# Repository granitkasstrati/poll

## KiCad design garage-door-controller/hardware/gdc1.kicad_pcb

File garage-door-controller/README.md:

# gdc1: open-source smart garage door controller (rev A)

A local-first retrofit controller that works with the opener you already have. A dry-contact relay presses the
wall button. Three opto-isolated reed inputs sense the door. An ESP32-S3 connects it to MQTT/Home Assistant,
with no cloud.

| Path | What |
|---|---|
| `docs/DESIGN.md` | requirements → hardware map, **calculations**, pin map, **what to verify**, bring-up, installation |
| `docs/PCB.md` | floor plan, layout rules, DRC status, how to regenerate |
| `hardware/gdc1.kicad_pro` | KiCad 7 project (schematic + PCB) |
| `hardware/fab/` | Gerbers + drill (zip), BOM CSV, pick-and-place, schematic/PCB PDFs, renders |
| `hardware/gen/` | Python generators. `design.py` is the single source of truth for parts and nets |
| `firmware/board_pins.h` | GPIO map for the ESP-IDF firmware (Phase 2/3 of the plan) |

**Board:** 105 × 85 mm, 2 layers, 1.6 mm FR4, 1 oz. 122 parts, mostly SMD 0603/0805/1206. The fine-pitch
parts are the ESP32-S3 module, the USB-C receptacle and the BME280 LGA (hot air recommended for that one).

**Highlights**
* Input: 9–36 VDC (either polarity) or 24 VAC → TPS54360 60 V buck. A USB-C alone also powers and flashes the board.
* Relay drive is AC-coupled in hardware, so a crashed MCU cannot hold the opener button "pressed" (SR4).
* Door inputs run from an isolated 1 W DC/DC, with a 2 mm isolation fence on the PCB. Each input has an LED
  that lights when its reed is closed, with or without firmware.
* Pre-close warning: on-board buzzer + red LED, plus a switched 12/24 V output for a strobe at the door (UL 325).
* BME280 sits in a thermally slotted corner. A Qwiic port takes a ToF sensor, and an expansion header
  takes a CT clamp or UART.

Licences: hardware CERN-OHL-S-2.0, firmware/scripts MIT.

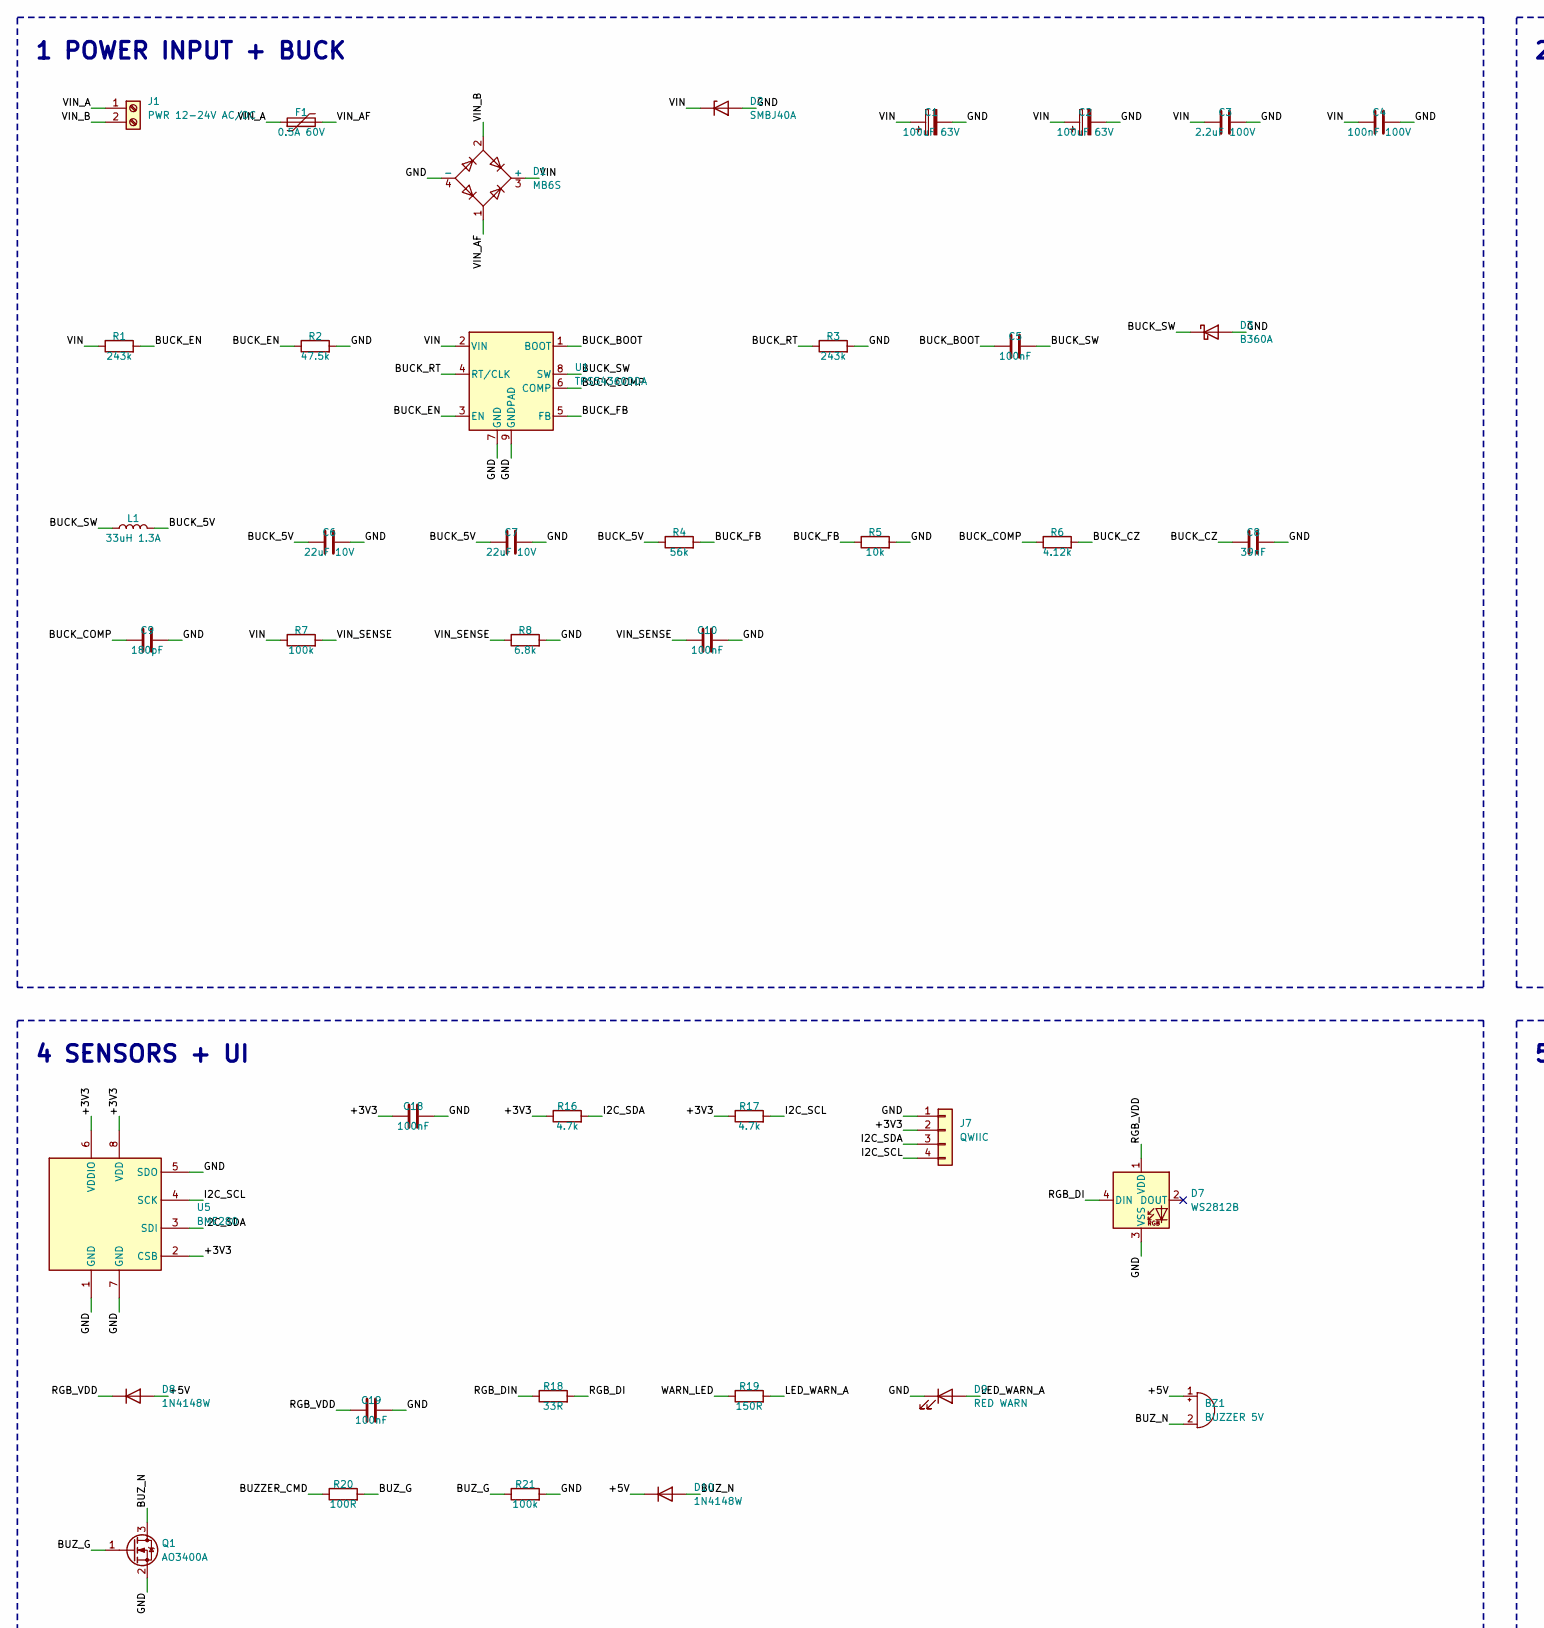
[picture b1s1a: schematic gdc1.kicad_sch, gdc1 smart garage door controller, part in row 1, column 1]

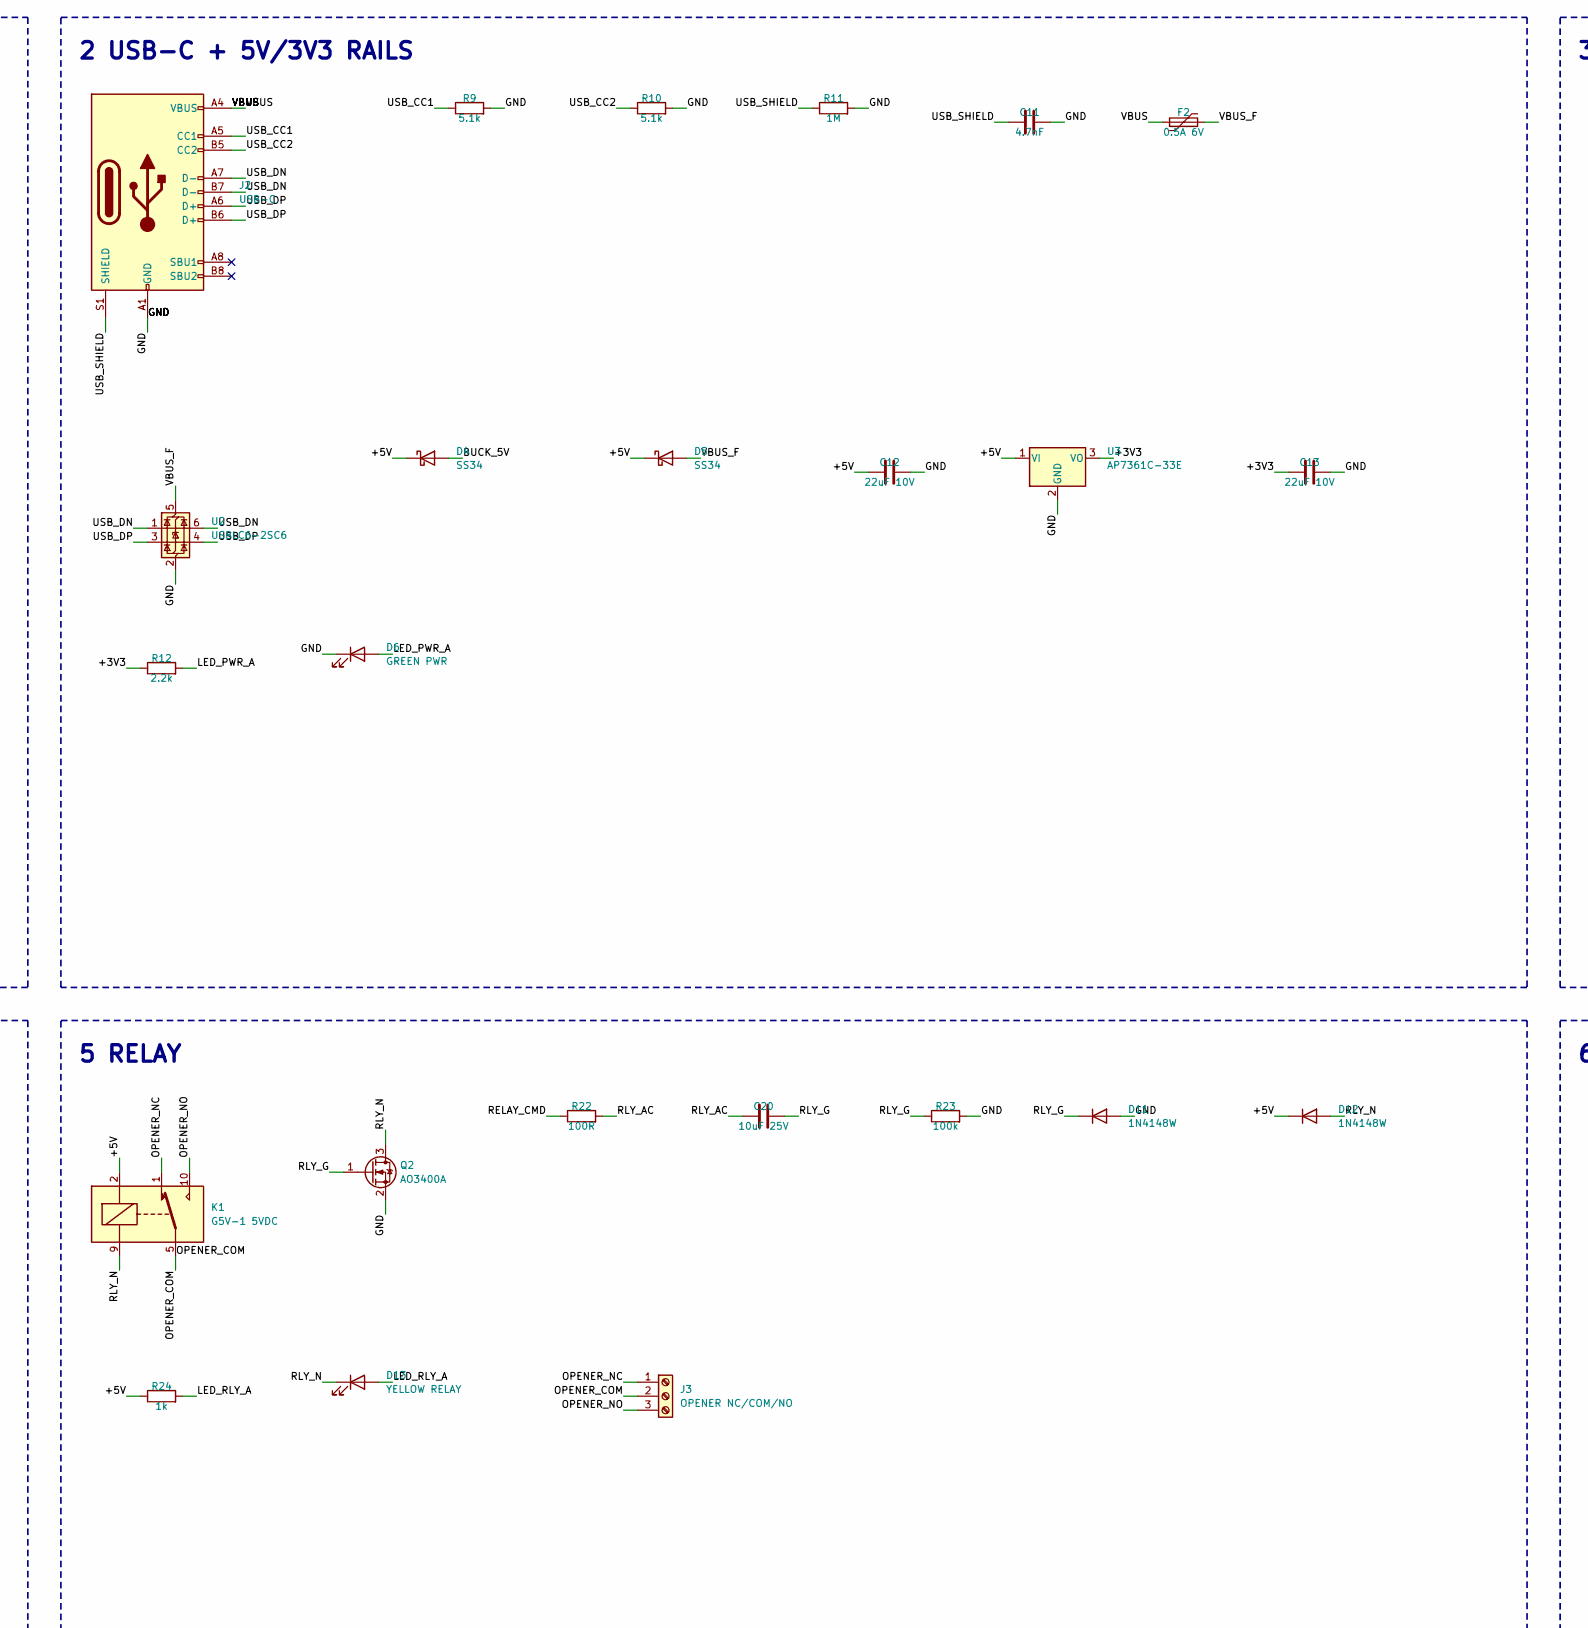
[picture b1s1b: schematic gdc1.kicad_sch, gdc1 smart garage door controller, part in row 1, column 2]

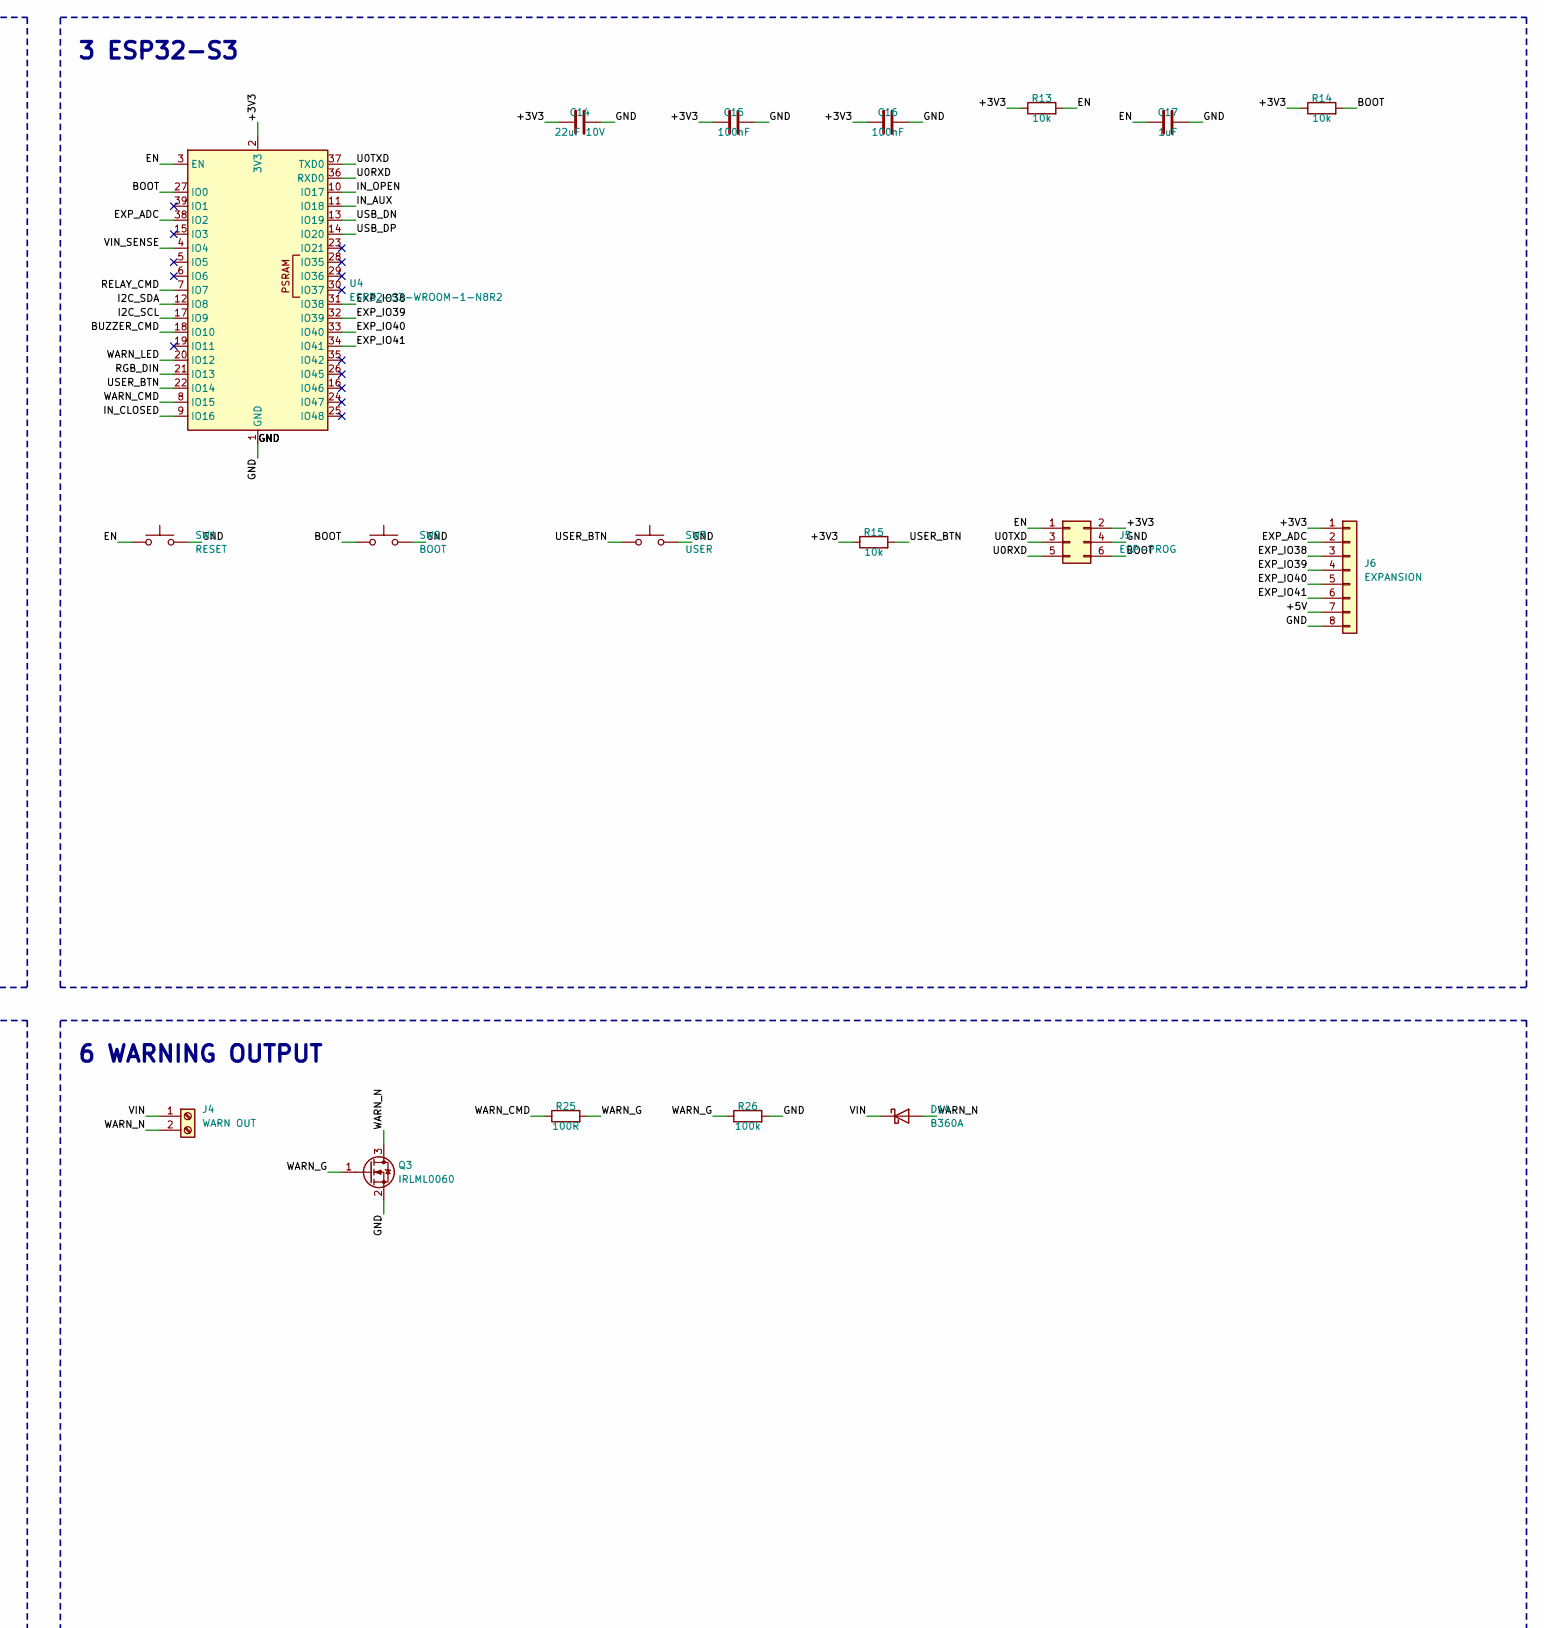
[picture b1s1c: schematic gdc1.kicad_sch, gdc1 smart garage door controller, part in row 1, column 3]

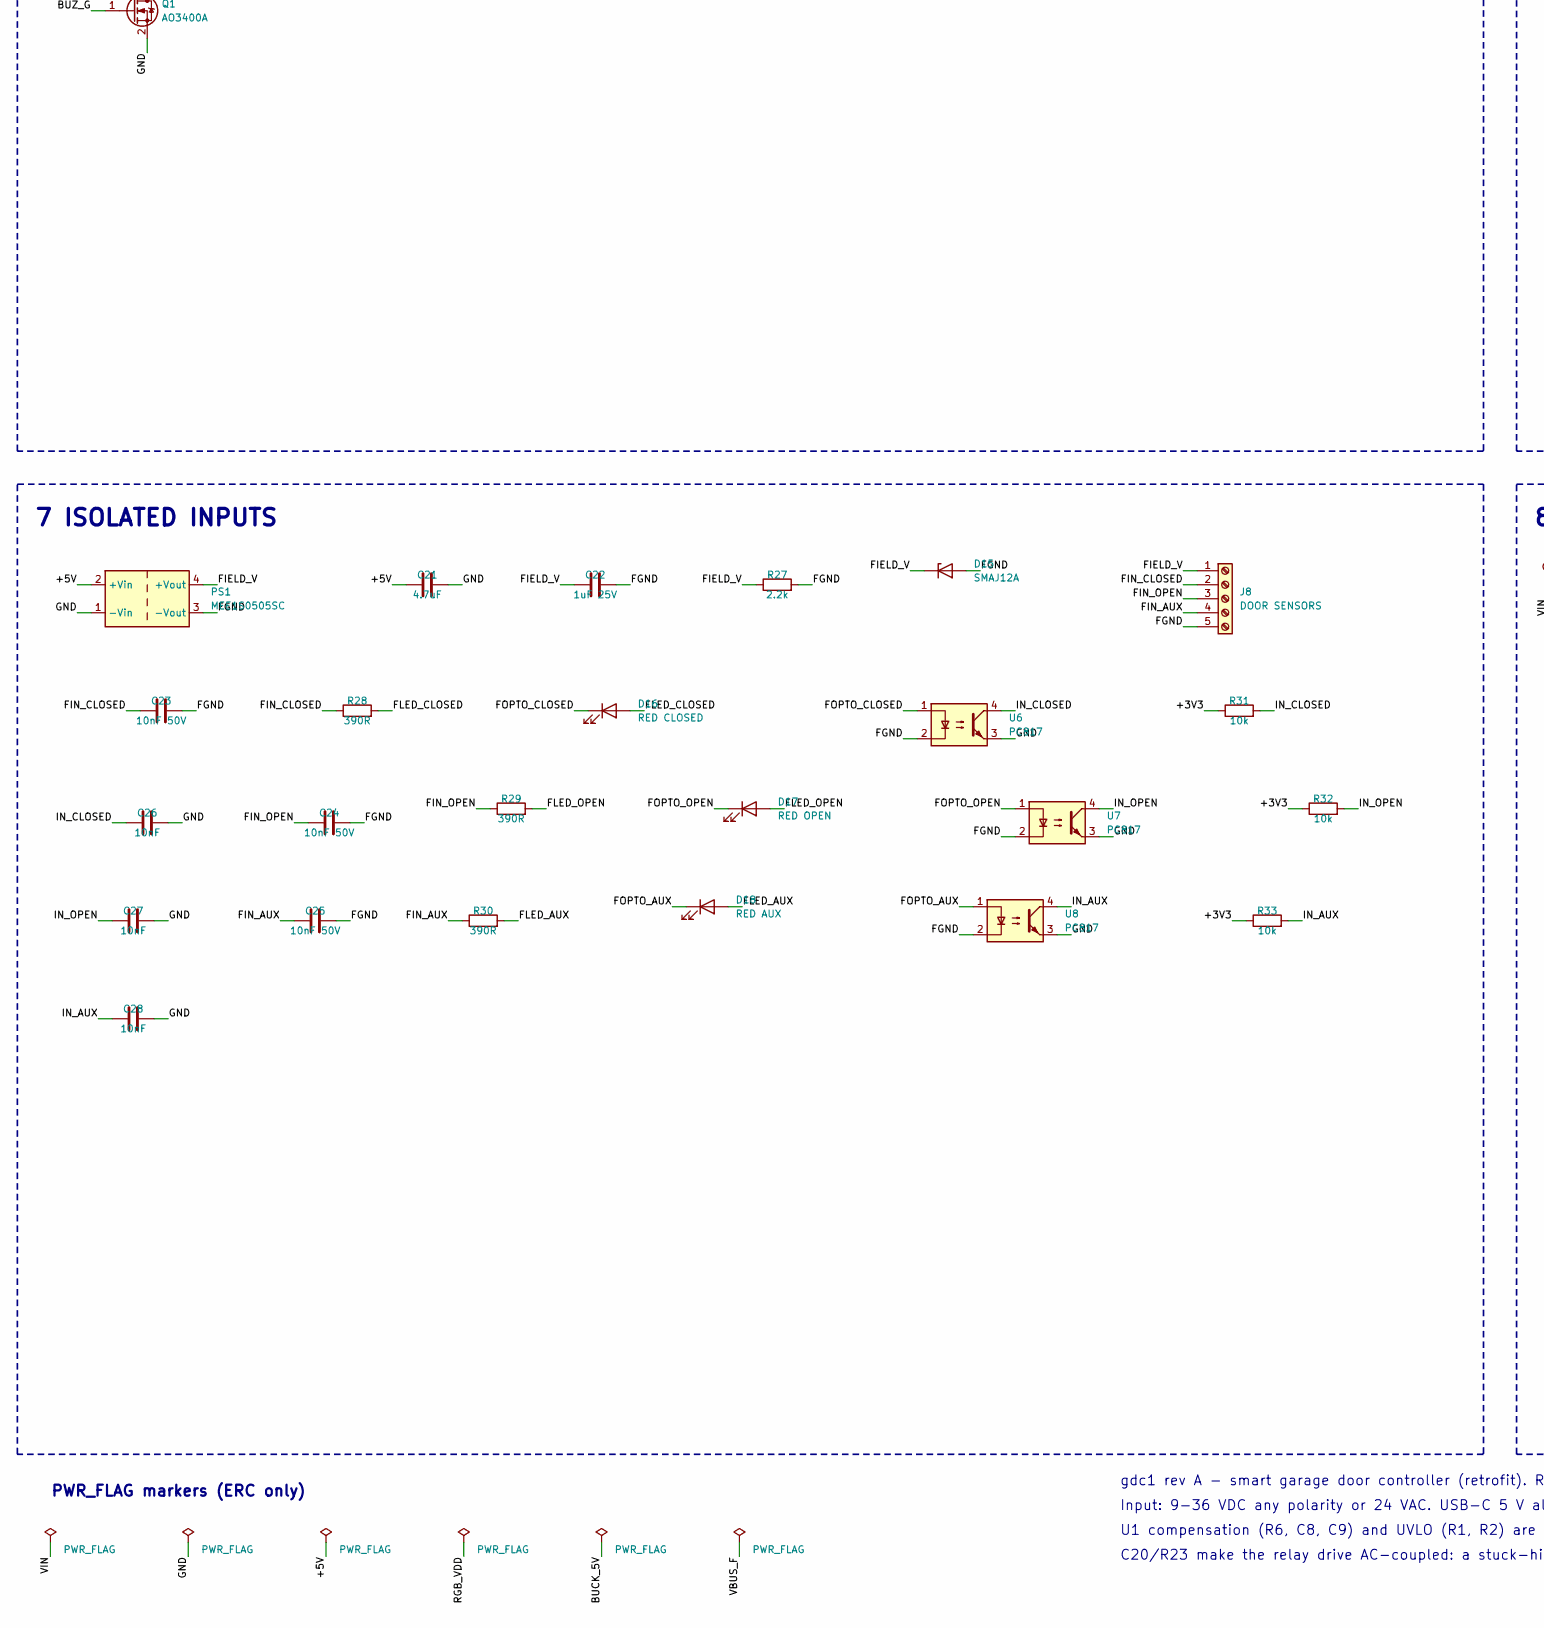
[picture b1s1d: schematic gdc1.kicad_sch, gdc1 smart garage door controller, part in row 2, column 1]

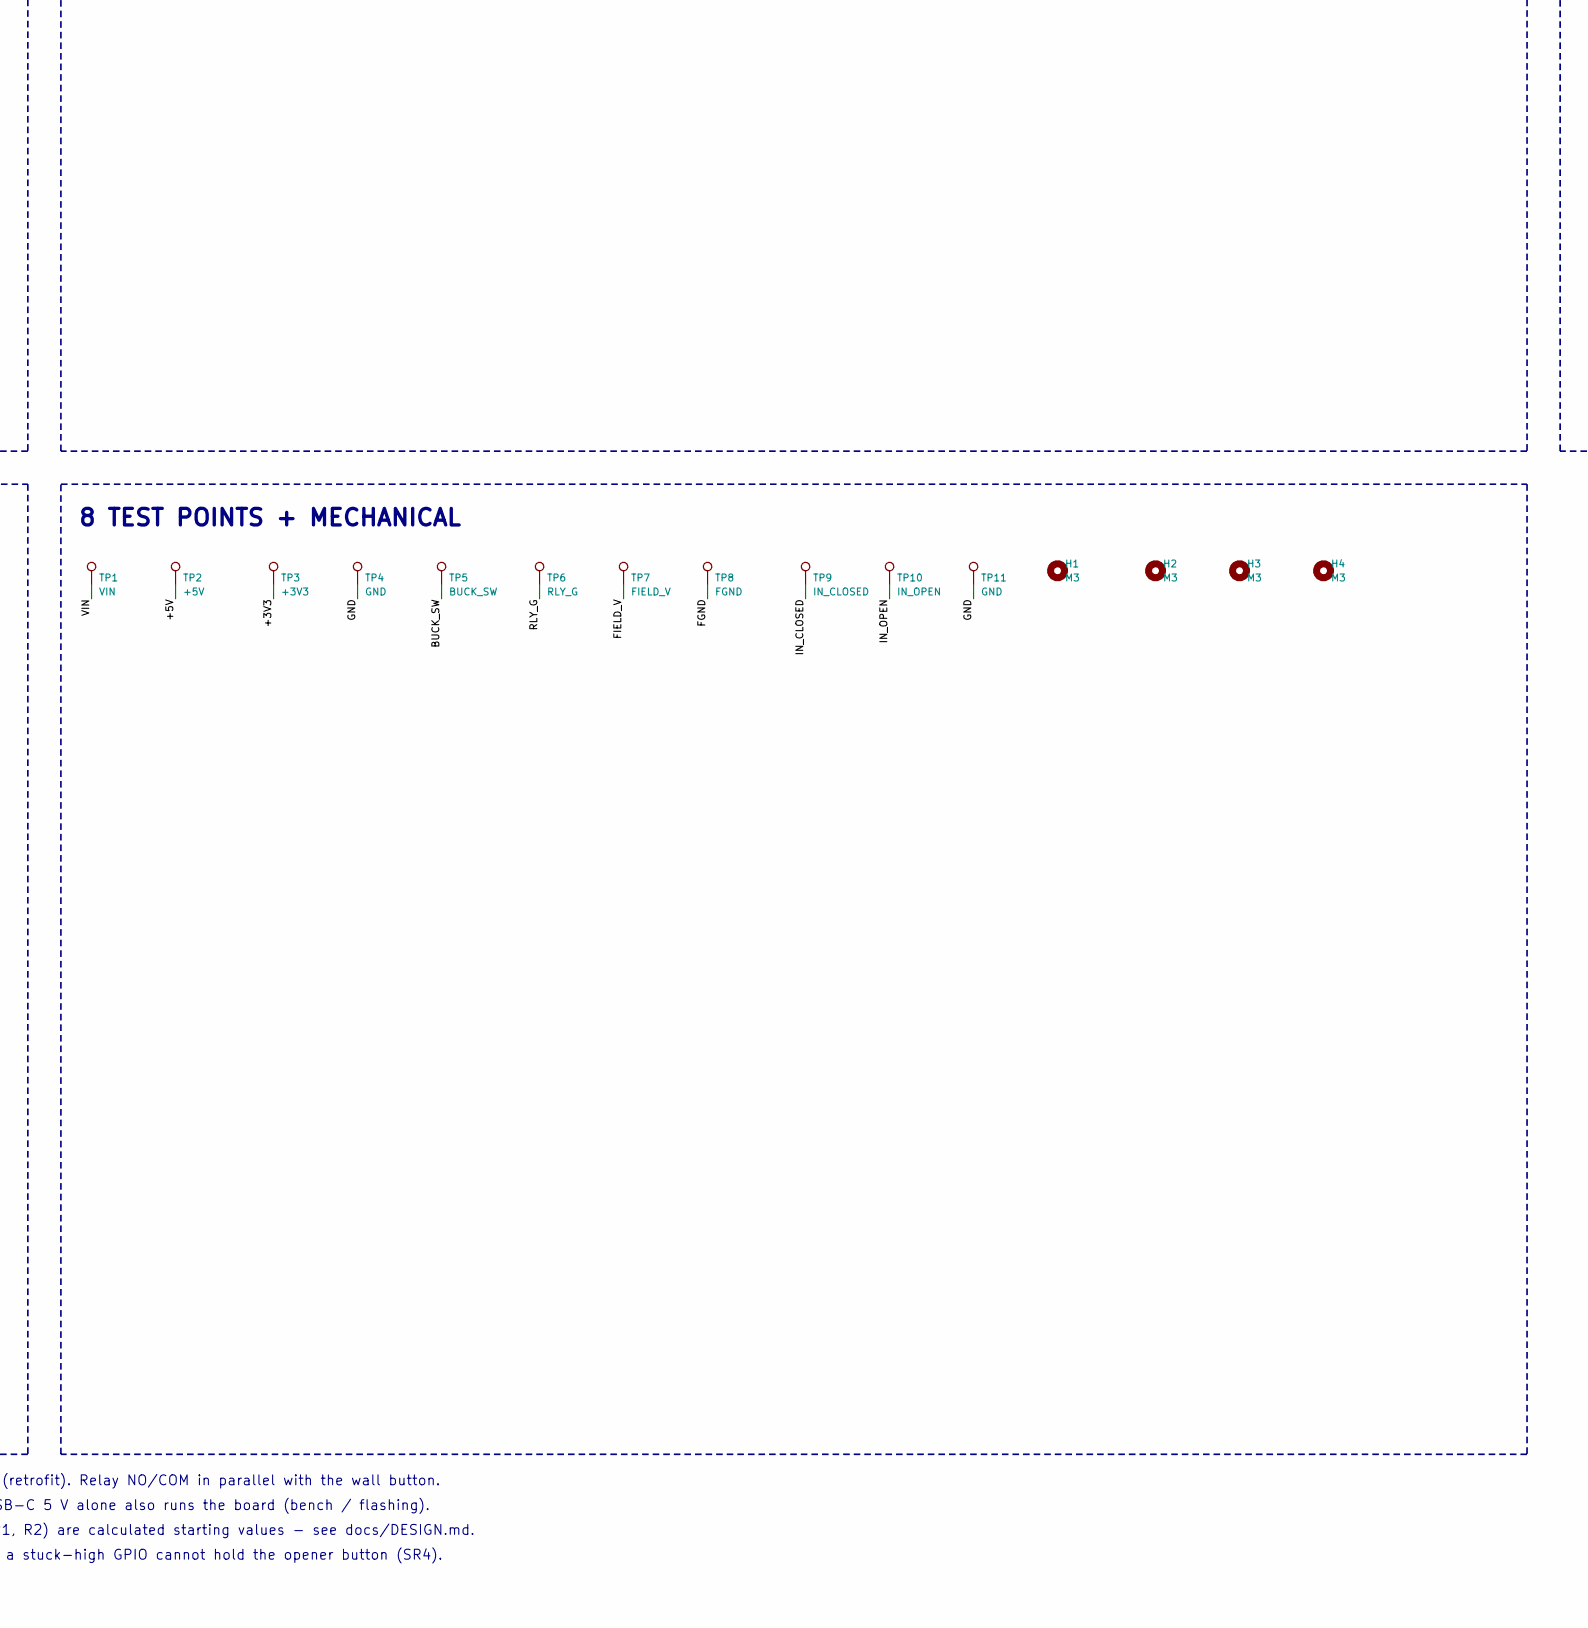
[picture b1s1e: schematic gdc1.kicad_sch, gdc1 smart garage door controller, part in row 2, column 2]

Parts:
BZ1: BUZZER 5V; Buzzer_12x9.5RM7.6; MPN CUI CMI-1295IC-0585T (5 V, 85 dB, self-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
C1: 100uF 63V; CP_Elec_10x10.5; MPN Panasonic EEE-FK1J101P (10x10.2, 105 C)
C2: 100uF 63V; CP_Elec_10x10.5; MPN Panasonic EEE-FK1J101P
C3: 2.2uF 100V; C_1210_3225Metric; MPN Murata GRM32ER72A225KA35 (X7R)
C4: 100nF 100V; C_0805_2012Metric
C5, C10, C15, C16, C18, C19: 100nF; C_0603_1608Metric
C6, C7: 22uF 10V; C_1210_3225Metric; MPN X7R 1210
C8: 39nF; C_0603_1608Metric
C9: 180pF; C_0603_1608Metric
C11: 4.7nF; C_0805_2012Metric
C12, C13, C14: 22uF 10V; C_1206_3216Metric
C17: 1uF; C_0603_1608Metric
C20: 10uF 25V; C_1206_3216Metric
C21: 4.7uF; C_0805_2012Metric
C22: 1uF 25V; C_0805_2012Metric
C23, C24, C25: 10nF 50V; C_0805_2012Metric
C26, C27, C28: 10nF; C_0603_1608Metric
D1: MB6S; TO-269AA; MPN Vishay/onsemi MB6S (0.5 A 600 V)
D2: SMBJ40A; D_SMB; MPN Littelfuse SMBJ40A
D3: B360A; D_SMA; MPN Diodes B360A-13-F (60 V 3 A)
D4, D5: SS34; D_SMA; MPN SS34 (40 V 3 A)
D6: GREEN PWR; LED_0805_2012Metric
D7: WS2812B; LED_WS2812B_PLCC4_5.0x5.0mm_P3.2mm; MPN Worldsemi WS2812B
D8, D10, D11, D12: 1N4148W; D_SOD-123
D9: RED WARN; LED_0805_2012Metric
D13: YELLOW RELAY; LED_0805_2012Metric
D14: B360A; D_SMA; MPN Diodes B360A-13-F
D15: SMAJ12A; D_SMA; MPN Littelfuse SMAJ12A
D16: RED CLOSED; LED_0805_2012Metric
D17: RED OPEN; LED_0805_2012Metric
D18: RED AUX; LED_0805_2012Metric
F1: 0.5A 60V; Fuse_Bourns_MF-RHT050; MPN Bourns MF-R050 (0.5 A hold, 60 V, radia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
F2: 0.5A 6V; Fuse_1206_3216Metric; MPN Littelfuse 1206L050YR
H1, H2, H3, H4: M3; MountingHole_3.2mm_M3
J1: PWR 12-24V AC/DC; TerminalBlock_Phoenix_MKDS-1,5-2-5.08_1x02_P5.08mm_Horizont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; MPN Phoenix MKDS 1,5/2-5,08 (1715721) or an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
J2: USB-C; USB_C_Receptacle_GCT_USB4105-xx-A_16P_TopMnt_Horizontal; MPN GCT USB4105-GF-A
J3: OPENER NC/COM/NO; TerminalBlock_Phoenix_MKDS-1,5-3-5.08_1x03_P5.08mm_Horizont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; MPN Phoenix MKDS 1,5/3-5,08
J4: WARN OUT; TerminalBlock_Phoenix_MKDS-1,5-2-5.08_1x02_P5.08mm_Horizont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; MPN Phoenix MKDS 1,5/2-5,08
J5: ESP-PROG; PinHeader_2x03_P2.54mm_Vertical
J6: EXPANSION; PinHeader_1x08_P2.54mm_Vertical
J7: QWIIC; JST_SH_SM04B-SRSS-TB_1x04-1MP_P1.00mm_Horizontal; MPN JST SM04B-SRSS-TB
J8: DOOR SENSORS; TerminalBlock_Phoenix_MKDS-1,5-5-5.08_1x05_P5.08mm_Horizont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; MPN Phoenix MKDS 1,5/5-5,08
K1: G5V-1 5VDC; Relay_SPDT_Omron_G5V-1; MPN Omron G5V-1-DC5
L1: 33uH 1.3A; L_Bourns_SRN6045TA; MPN Bourns SRN6045TA-330M
PS1: MEE1S0505SC; Converter_DCDC_Murata_MEE1SxxxxSC_THT; MPN Murata MEE1S0505SC (1 W, 3 kVDC)
Q1, Q2: AO3400A; SOT-23; MPN AO3400A
Q3: IRLML0060; SOT-23; MPN Infineon IRLML0060TRPBF (60 V)
R1, R3: 243k; R_0603_1608Metric
R2: 47.5k; R_0603_1608Metric
R4: 56k; R_0603_1608Metric
R5, R13, R14, R15, R31, R32, R33: 10k; R_0603_1608Metric
R6: 4.12k; R_0603_1608Metric
R7, R21, R23, R26: 100k; R_0603_1608Metric
R8: 6.8k; R_0603_1608Metric
R9, R10: 5.1k; R_0603_1608Metric
R11: 1M; R_0603_1608Metric
R12: 2.2k; R_0603_1608Metric
R16, R17: 4.7k; R_0603_1608Metric
R18: 33R; R_0603_1608Metric
R19: 150R; R_0603_1608Metric
R20, R22, R25: 100R; R_0603_1608Metric
R24: 1k; R_0603_1608Metric
R27: 2.2k; R_0805_2012Metric
R28, R29, R30: 390R; R_1206_3216Metric
SW1: RESET; SW_SPST_TL3342; MPN E-Switch TL3342
SW2: BOOT; SW_SPST_TL3342; MPN E-Switch TL3342
SW3: USER; SW_SPST_TL3342; MPN E-Switch TL3342
TP1: VIN; TestPoint_Pad_D1.5mm
TP2: +5V; TestPoint_Pad_D1.5mm
TP3: +3V3; TestPoint_Pad_D1.5mm
TP4, TP11: GND; TestPoint_Pad_D1.5mm
TP5: BUCK_SW; TestPoint_Pad_D1.5mm
TP6: RLY_G; TestPoint_Pad_D1.5mm
TP7: FIELD_V; TestPoint_Pad_D1.5mm
TP8: FGND; TestPoint_Pad_D1.5mm
TP9: IN_CLOSED; TestPoint_Pad_D1.5mm
TP10: IN_OPEN; TestPoint_Pad_D1.5mm
U1: TPS54360DDA; TI_SO-PowerPAD-8_ThermalVias; MPN TI TPS54360DDAR (4.5-60 V, 3.5 A)
U2: USBLC6-2SC6; SOT-23-6; MPN ST USBLC6-2SC6
U3: AP7361C-33E; SOT-223-3_TabPin2; MPN Diodes AP7361C-33E-13 (1 A, 0.36 V drop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
U4: ESP32-S3-WROOM-1-N8R2; ESP32-S3-WROOM-1; MPN Espressif ESP32-S3-WROOM-1-N8R2
U5: BME280; Bosch_LGA-8_2.5x2.5mm_P0.65mm_ClockwisePinNumbering; MPN Bosch BME280
U6, U7, U8: PC817; SMDIP-4_W9.53mm; MPN Sharp/Everlight PC817 (gull-wing)

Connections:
+3V3: C13.1, C14.1, C15.1, C16.1, C18.1, J5.2, J6.1, J7.2, R12.1, R13.1, R14.1, R15.1, R16.1, R17.1, R31.1, R32.1, R33.1, TP3.1, U3.3 (VO), U4.2 (3V3), U5.2 (CSB), U5.6 (VDDIO), U5.8 (VDD)
+5V: BZ1.1 (+), C12.1, C21.1, D4.1 (K), D5.1 (K), D8.2 (A), D10.1 (K), D12.1 (K), J6.7, K1.2, PS1.2 (+Vin), R24.1, TP2.1, U3.1 (VI)
BOOT: J5.6, R14.2, SW2.1, U4.27 (IO0)
BUCK_5V: C6.1, C7.1, D4.2 (A), L1.2, R4.1
BUCK_BOOT: C5.1, U1.1 (BOOT)
BUCK_COMP: C9.1, R6.1, U1.6 (COMP)
BUCK_CZ: C8.1, R6.2
BUCK_EN: R1.2, R2.1, U1.3 (EN)
BUCK_FB: R4.2, R5.1, U1.5 (FB)
BUCK_RT: R3.1, U1.4 (RT/CLK)
BUCK_SW: C5.2, D3.1 (K), L1.1, TP5.1, U1.8 (SW)
BUZZER_CMD: R20.1, U4.18 (IO10)
BUZ_G: Q1.1 (G), R20.2, R21.1
BUZ_N: BZ1.2 (-), D10.2 (A), Q1.3 (D)
EN: C17.1, J5.1, R13.2, SW1.1, U4.3 (EN)
EXP_ADC: J6.2, U4.38 (IO2)
EXP_IO38: J6.3, U4.31 (IO38)
EXP_IO39: J6.4, U4.32 (IO39)
EXP_IO40: J6.5, U4.33 (IO40)
EXP_IO41: J6.6, U4.34 (IO41)
FGND: C22.2, C23.2, C24.2, C25.2, D15.2 (A), J8.5, PS1.3 (-Vout), R27.2, TP8.1, U6.2, U7.2, U8.2
FIELD_V: C22.1, D15.1 (K), J8.1, PS1.4 (+Vout), R27.1, TP7.1
FIN_AUX: C25.1, J8.4, R30.1
FIN_CLOSED: C23.1, J8.2, R28.1
FIN_OPEN: C24.1, J8.3, R29.1
FLED_AUX: D18.2 (A), R30.2
FLED_CLOSED: D16.2 (A), R28.2
FLED_OPEN: D17.2 (A), R29.2
FOPTO_AUX: D18.1 (K), U8.1
FOPTO_CLOSED: D16.1 (K), U6.1
FOPTO_OPEN: D17.1 (K), U7.1
GND: C1.2, C2.2, C3.2, C4.2, C6.2, C7.2, C8.2, C9.2, C10.2, C11.2, C12.2, C13.2, C14.2, C15.2, C16.2, C17.2, C18.2, C19.2, C21.2, C26.2, C27.2, C28.2, D1.4 (-), D2.2 (A), D3.2 (A), D6.1 (K), D7.3 (VSS), D9.1 (K), D11.2 (A), J2.A1 (GND), J2.A12 (GND), J2.B1 (GND), J2.B12 (GND), J5.4, J6.8, J7.1, PS1.1 (-Vin), Q1.2 (S), Q2.2 (S), Q3.2 (S), R2.2, R3.2, R5.2, R8.2, R9.2, R10.2, R11.2, R21.2, R23.2, R26.2, SW1.2, SW2.2, SW3.2, TP4.1, TP11.1, U1.7 (GND), U1.9 (GNDPAD), U2.2 (GND), U3.2 (GND), U4.1 (GND), U4.40 (GND), U4.41 (GND), U5.1 (GND), U5.5 (SDO), U5.7 (GND), U6.3, U7.3, U8.3
I2C_SCL: J7.4, R17.2, U4.17 (IO9), U5.4 (SCK)
I2C_SDA: J7.3, R16.2, U4.12 (IO8), U5.3 (SDI)
IN_AUX: C28.1, R33.2, U4.11 (IO18), U8.4
IN_CLOSED: C26.1, R31.2, TP9.1, U4.9 (IO16), U6.4
IN_OPEN: C27.1, R32.2, TP10.1, U4.10 (IO17), U7.4
LED_PWR_A: D6.2 (A), R12.2
LED_RLY_A: D13.2 (A), R24.2
LED_WARN_A: D9.2 (A), R19.2
OPENER_COM: J3.2, K1.5, K1.6
OPENER_NC: J3.1, K1.1
OPENER_NO: J3.3, K1.10
RELAY_CMD: R22.1, U4.7 (IO7)
RGB_DI: D7.4 (DIN), R18.2
RGB_DIN: R18.1, U4.21 (IO13)
RGB_VDD: C19.1, D7.1 (VDD), D8.1 (K)
RLY_AC: C20.1, R22.2
RLY_G: C20.2, D11.1 (K), Q2.1 (G), R23.1, TP6.1
RLY_N: D12.2 (A), D13.1 (K), K1.9, Q2.3 (D)
U0RXD: J5.5, U4.36 (RXD0)
U0TXD: J5.3, U4.37 (TXD0)
USB_CC1: J2.A5 (CC1), R9.1
USB_CC2: J2.B5 (CC2), R10.1
USB_DN: J2.A7 (D-), J2.B7 (D-), U2.1 (I/O1), U2.6 (I/O1), U4.13 (IO19)
USB_DP: J2.A6 (D+), J2.B6 (D+), U2.3 (I/O2), U2.4 (I/O2), U4.14 (IO20)
USB_SHIELD: C11.1, J2.S1 (SHIELD), R11.1
USER_BTN: R15.2, SW3.1, U4.22 (IO14)
VBUS: F2.1, J2.A4 (VBUS), J2.A9 (VBUS), J2.B4 (VBUS), J2.B9 (VBUS)
VBUS_F: D5.2 (A), F2.2, U2.5 (VBUS)
VIN: C1.1, C2.1, C3.1, C4.1, D1.3 (+), D2.1 (K), D14.1 (K), J4.1, R1.1, R7.1, TP1.1, U1.2 (VIN)
VIN_A: F1.1, J1.1
VIN_AF: D1.1, F1.2
VIN_B: D1.2, J1.2
VIN_SENSE: C10.1, R7.2, R8.1, U4.4 (IO4)
WARN_CMD: R25.1, U4.8 (IO15)
WARN_G: Q3.1 (G), R25.2, R26.1
WARN_LED: R19.1, U4.20 (IO12)
WARN_N: D14.2 (A), J4.2, Q3.3 (D)

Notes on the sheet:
1 POWER INPUT + BUCK
2 USB-C + 5V/3V3 RAILS
3 ESP32-S3
4 SENSORS + UI
5 RELAY
6 WARNING OUTPUT
7 ISOLATED INPUTS
8 TEST POINTS + MECHANICAL
PWR_FLAG markers (ERC only)
gdc1 rev A - smart garage door controller (retrofit). Relay NO/COM in parallel with the wall button.
Input: 9-36 VDC any polarity or 24 VAC. USB-C 5 V alone also runs the board (bench / flashing).
U1 compensation (R6, C8, C9) and UVLO (R1, R2) are calculated starting values - see docs/DESIGN.md.
C20/R23 make the relay drive AC-coupled: a stuck-high GPIO cannot hold the opener button (SR4).

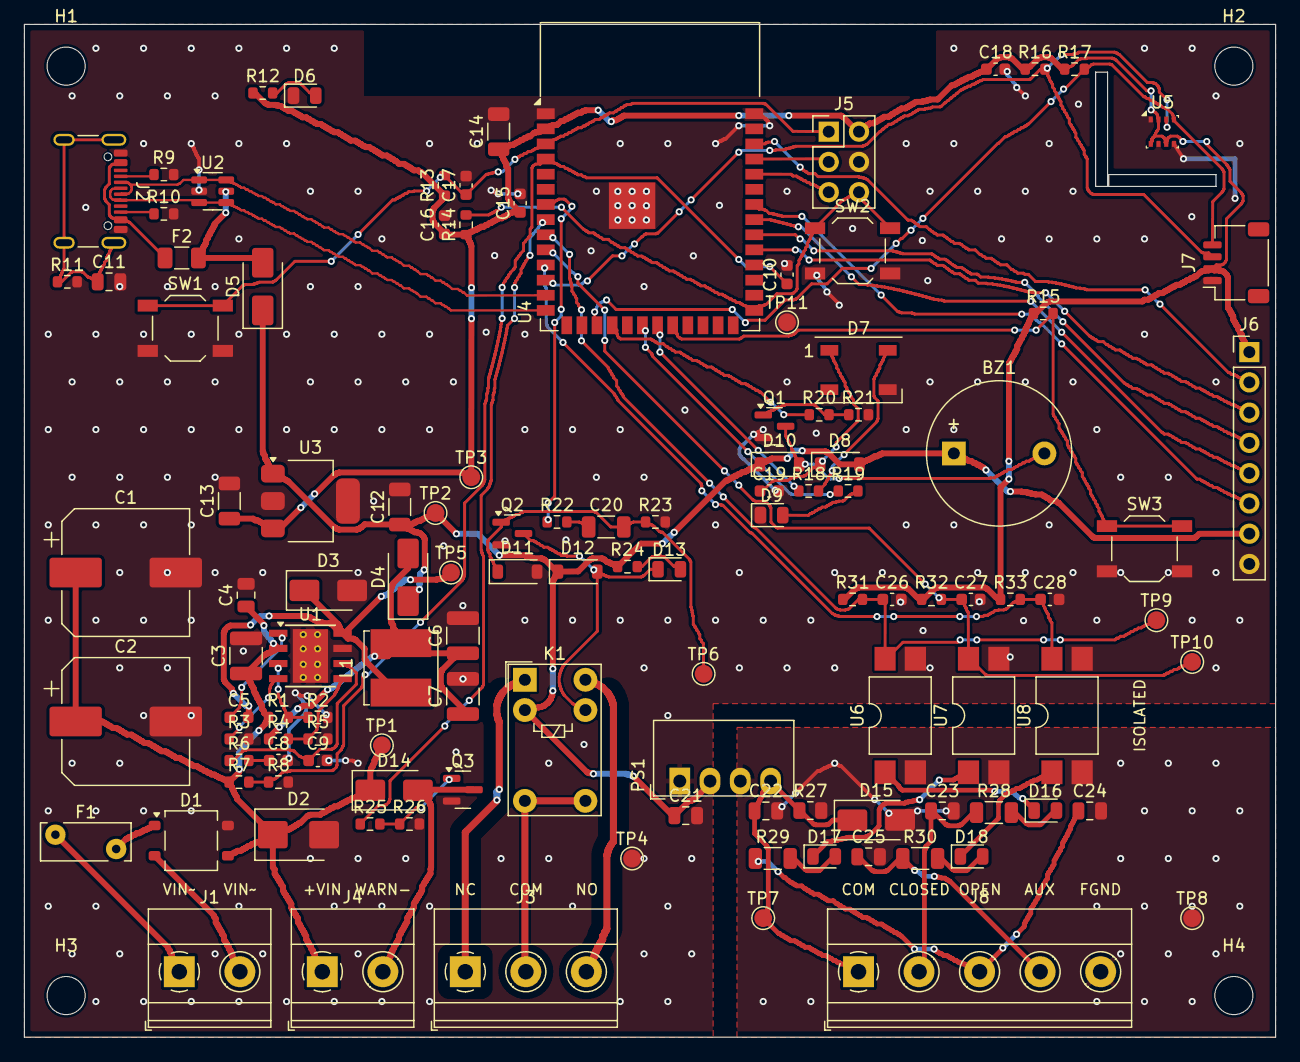
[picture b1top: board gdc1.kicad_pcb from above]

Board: 2 copper layers, 105.0 x 85.0 mm, 122 parts (0 on the bottom side), 69 nets.

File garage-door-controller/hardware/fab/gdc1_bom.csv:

Qty,References,Value,Footprint,MPN / suggestion,Notes
1,BZ1,BUZZER 5V,Buzzer_12x9.5RM7.6,"CUI CMI-1295IC-0585T (5 V, 85 dB, self-drive)",
1,C1,100uF 63V,CP_Elec_10x10.5,"Panasonic EEE-FK1J101P (10x10.2, 105 C)",
1,C2,100uF 63V,CP_Elec_10x10.5,Panasonic EEE-FK1J101P,2nd bulk cap: holds VIN up between 24 VAC half-cycles
1,C3,2.2uF 100V,C_1210_3225Metric,Murata GRM32ER72A225KA35 (X7R),place at U1 VIN/GND
1,C4,100nF 100V,C_0805_2012Metric,,
6,C5 C10 C15 C16 C18 C19,100nF,C_0603_1608Metric,,C5: bootstrap
2,C6 C7,22uF 10V,C_1210_3225Metric,X7R 1210,
1,C8,39nF,C_0603_1608Metric,,
1,C9,180pF,C_0603_1608Metric,,
1,C11,4.7nF,C_0805_2012Metric,,
3,C12 C13 C14,22uF 10V,C_1206_3216Metric,,C14: Wi-Fi TX burst reservoir
1,C17,1uF,C_0603_1608Metric,,EN delay per Espressif HW guide
1,C20,10uF 25V,C_1206_3216Metric,,AC coupling: a GPIO stuck high releases the relay after ~0.7 s (SR4)
1,C21,4.7uF,C_0805_2012Metric,,
1,C22,1uF 25V,C_0805_2012Metric,,
3,C23 C24 C25,10nF 50V,C_0805_2012Metric,,C23: field-side HF filter; C24: field-side HF filter; C25: field-side HF filter
3,C26 C27 C28,10nF,C_0603_1608Metric,,
1,D1,MB6S,TO-269AA,Vishay/onsemi MB6S (0.5 A 600 V),makes the input polarity-proof and accepts 24 VAC
1,D2,SMBJ40A,D_SMB,Littelfuse SMBJ40A,"40 V standoff, 44.4 V min breakdown; above 24 VAC +10 % / +15 % no-load peak (41.6 V)"
1,D3,B360A,D_SMA,Diodes B360A-13-F (60 V 3 A),catch diode
2,D4 D5,SS34,D_SMA,SS34 (40 V 3 A),D4: OR-ing: buck path; D5: OR-ing: USB path
1,D6,GREEN PWR,LED_0805_2012Metric,,
1,D7,WS2812B,LED_WS2812B_PLCC4_5.0x5.0mm_P3.2mm,Worldsemi WS2812B,status LED
4,D8 D10 D11 D12,1N4148W,D_SOD-123,,D8: drops VDD to ~4.3 V so 3.3 V logic meets VIH = 0.7 VDD; D11: clamps the negative gate swing so the next pulse is full height; D12: coil flyback
1,D9,RED WARN,LED_0805_2012Metric,,flashes during the pre-close warning (SR1)
1,D13,YELLOW RELAY,LED_0805_2012Metric,,
1,D14,B360A,D_SMA,Diodes B360A-13-F,freewheel for inductive sounders
1,D15,SMAJ12A,D_SMA,Littelfuse SMAJ12A,
1,D16,RED CLOSED,LED_0805_2012Metric,,"lights when the reed closes, with or without firmware"
1,D17,RED OPEN,LED_0805_2012Metric,,"lights when the reed closes, with or without firmware"
1,D18,RED AUX,LED_0805_2012Metric,,"lights when the reed closes, with or without firmware"
1,F1,0.5A 60V,Fuse_Bourns_MF-RHT050,"Bourns MF-R050 (0.5 A hold, 60 V, radial 5.1 mm)",
1,F2,0.5A 6V,Fuse_1206_3216Metric,Littelfuse 1206L050YR,
4,H1 H2 H3 H4,M3,MountingHole_3.2mm_M3,,
1,J1,PWR 12-24V AC/DC,"TerminalBlock_Phoenix_MKDS-1,5-2-5.08_1x02_P5.08mm_Horizontal","Phoenix MKDS 1,5/2-5,08 (1715721) or any 5.08 mm clone","Any polarity DC 9-36 V, or 24 VAC (opener accessory / class-2 transformer)"
1,J2,USB-C,USB_C_Receptacle_GCT_USB4105-xx-A_16P_TopMnt_Horizontal,GCT USB4105-GF-A,native USB of the ESP32-S3: power + flashing + JTAG
1,J3,OPENER NC/COM/NO,"TerminalBlock_Phoenix_MKDS-1,5-3-5.08_1x03_P5.08mm_Horizontal","Phoenix MKDS 1,5/3-5,08",COM+NO in parallel with the wall button
1,J4,WARN OUT,"TerminalBlock_Phoenix_MKDS-1,5-2-5.08_1x02_P5.08mm_Horizontal","Phoenix MKDS 1,5/2-5,08","VIN (rectified), low-side switched, 300 mA"
1,J5,ESP-PROG,PinHeader_2x03_P2.54mm_Vertical,,"ESP-Prog 'Program' pinout: 1 EN, 2 VDD, 3 TXD, 4 GND, 5 RXD, 6 IO0 (auto-reset is on the ESP-Prog)"
1,J6,EXPANSION,PinHeader_1x08_P2.54mm_Vertical,,"CT clamp (IO2 = ADC1), UART1 (IO40/41), spare GPIO"
1,J7,QWIIC,JST_SH_SM04B-SRSS-TB_1x04-1MP_P1.00mm_Horizontal,JST SM04B-SRSS-TB,Qwiic/STEMMA QT: e.g. VL53L1X time-of-flight door observer
1,J8,DOOR SENSORS,"TerminalBlock_Phoenix_MKDS-1,5-5-5.08_1x05_P5.08mm_Horizontal","Phoenix MKDS 1,5/5-5,08",reed switches from COM (pin 1) to each input; pin 5 = cable shield
1,K1,G5V-1 5VDC,Relay_SPDT_Omron_G5V-1,Omron G5V-1-DC5,contacts 0.5 A 125 VAC / 1 A 24 VDC; only OPENER_* nets touch them
1,L1,33uH 1.3A,L_Bourns_SRN6045TA,Bourns SRN6045TA-330M,
1,PS1,MEE1S0505SC,Converter_DCDC_Murata_MEE1SxxxxSC_THT,"Murata MEE1S0505SC (1 W, 3 kVDC)",
2,Q1 Q2,AO3400A,SOT-23,AO3400A,
1,Q3,IRLML0060,SOT-23,Infineon IRLML0060TRPBF (60 V),
2,R1 R3,243k,R_0603_1608Metric,,"R1: UVLO: start 7.0 V, stop 6.0 V; R3: fsw = 400 kHz"
1,R2,47.5k,R_0603_1608Metric,,
1,R4,56k,R_0603_1608Metric,,Vout = 0.8*(1+56/10) = 5.28 V
7,R5 R13 R14 R15 R31 R32 R33,10k,R_0603_1608Metric,,
1,R6,4.12k,R_0603_1608Metric,,"type II comp, fco ~14 kHz"
4,R7 R21 R23 R26,100k,R_0603_1608Metric,,R7: VIN/15.7 -> ADC (45 V = 2.87 V); R23: tau = 1 s; also holds the FET off through reset/boot
1,R8,6.8k,R_0603_1608Metric,,
2,R9 R10,5.1k,R_0603_1608Metric,,R9: UFP Rd; R10: UFP Rd
1,R11,1M,R_0603_1608Metric,,
1,R12,2.2k,R_0603_1608Metric,,
2,R16 R17,4.7k,R_0603_1608Metric,,
1,R18,33R,R_0603_1608Metric,,
1,R19,150R,R_0603_1608Metric,,
3,R20 R22 R25,100R,R_0603_1608Metric,,
1,R24,1k,R_0603_1608Metric,,
1,R27,2.2k,R_0805_2012Metric,,pre-load keeps the unregulated output near 5 V
3,R28 R29 R30,390R,R_1206_3216Metric,,"R28: ~6 mA loop, 1206 for surge; R29: ~6 mA loop, 1206 for surge; R30: ~6 mA loop, 1206 for surge"
1,SW1,RESET,SW_SPST_TL3342,E-Switch TL3342,
1,SW2,BOOT,SW_SPST_TL3342,E-Switch TL3342,
1,SW3,USER,SW_SPST_TL3342,E-Switch TL3342,hold 10 s at boot = factory reset / provisioning portal
1,TP1,VIN,TestPoint_Pad_D1.5mm,,
1,TP2,+5V,TestPoint_Pad_D1.5mm,,
1,TP3,+3V3,TestPoint_Pad_D1.5mm,,
2,TP4 TP11,GND,TestPoint_Pad_D1.5mm,,
1,TP5,BUCK_SW,TestPoint_Pad_D1.5mm,,
1,TP6,RLY_G,TestPoint_Pad_D1.5mm,,
1,TP7,FIELD_V,TestPoint_Pad_D1.5mm,,
1,TP8,FGND,TestPoint_Pad_D1.5mm,,
1,TP9,IN_CLOSED,TestPoint_Pad_D1.5mm,,
1,TP10,IN_OPEN,TestPoint_Pad_D1.5mm,,
1,U1,TPS54360DDA,TI_SO-PowerPAD-8_ThermalVias,"TI TPS54360DDAR (4.5-60 V, 3.5 A)",
1,U2,USBLC6-2SC6,SOT-23-6,ST USBLC6-2SC6,
1,U3,AP7361C-33E,SOT-223-3_TabPin2,"Diodes AP7361C-33E-13 (1 A, 0.36 V dropout)",
1,U4,ESP32-S3-WROOM-1-N8R2,ESP32-S3-WROOM-1,Espressif ESP32-S3-WROOM-1-N8R2,"antenna over the board edge, no copper under it"
1,U5,BME280,Bosch_LGA-8_2.5x2.5mm_P0.65mm_ClockwisePinNumbering,Bosch BME280,I2C addr 0x76 (SDO=GND); thermally isolated by slots
3,U6 U7 U8,PC817,SMDIP-4_W9.53mm,Sharp/Everlight PC817 (gull-wing),
